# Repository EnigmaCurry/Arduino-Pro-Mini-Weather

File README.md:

Arduino Pro-Mini Enviromental Display Project
========================

This is an arduino project to build a miniature environment sensor
module to display temperature, barometric pressure, and humidity.

All files contained herein produced by
[R&TPreppers](https://www.youtube.com/channel/UCTNV_Oh5QAi1Is9r9Aw5bpw)
/ [njsharkracer](https://github.com/njsharkracer)

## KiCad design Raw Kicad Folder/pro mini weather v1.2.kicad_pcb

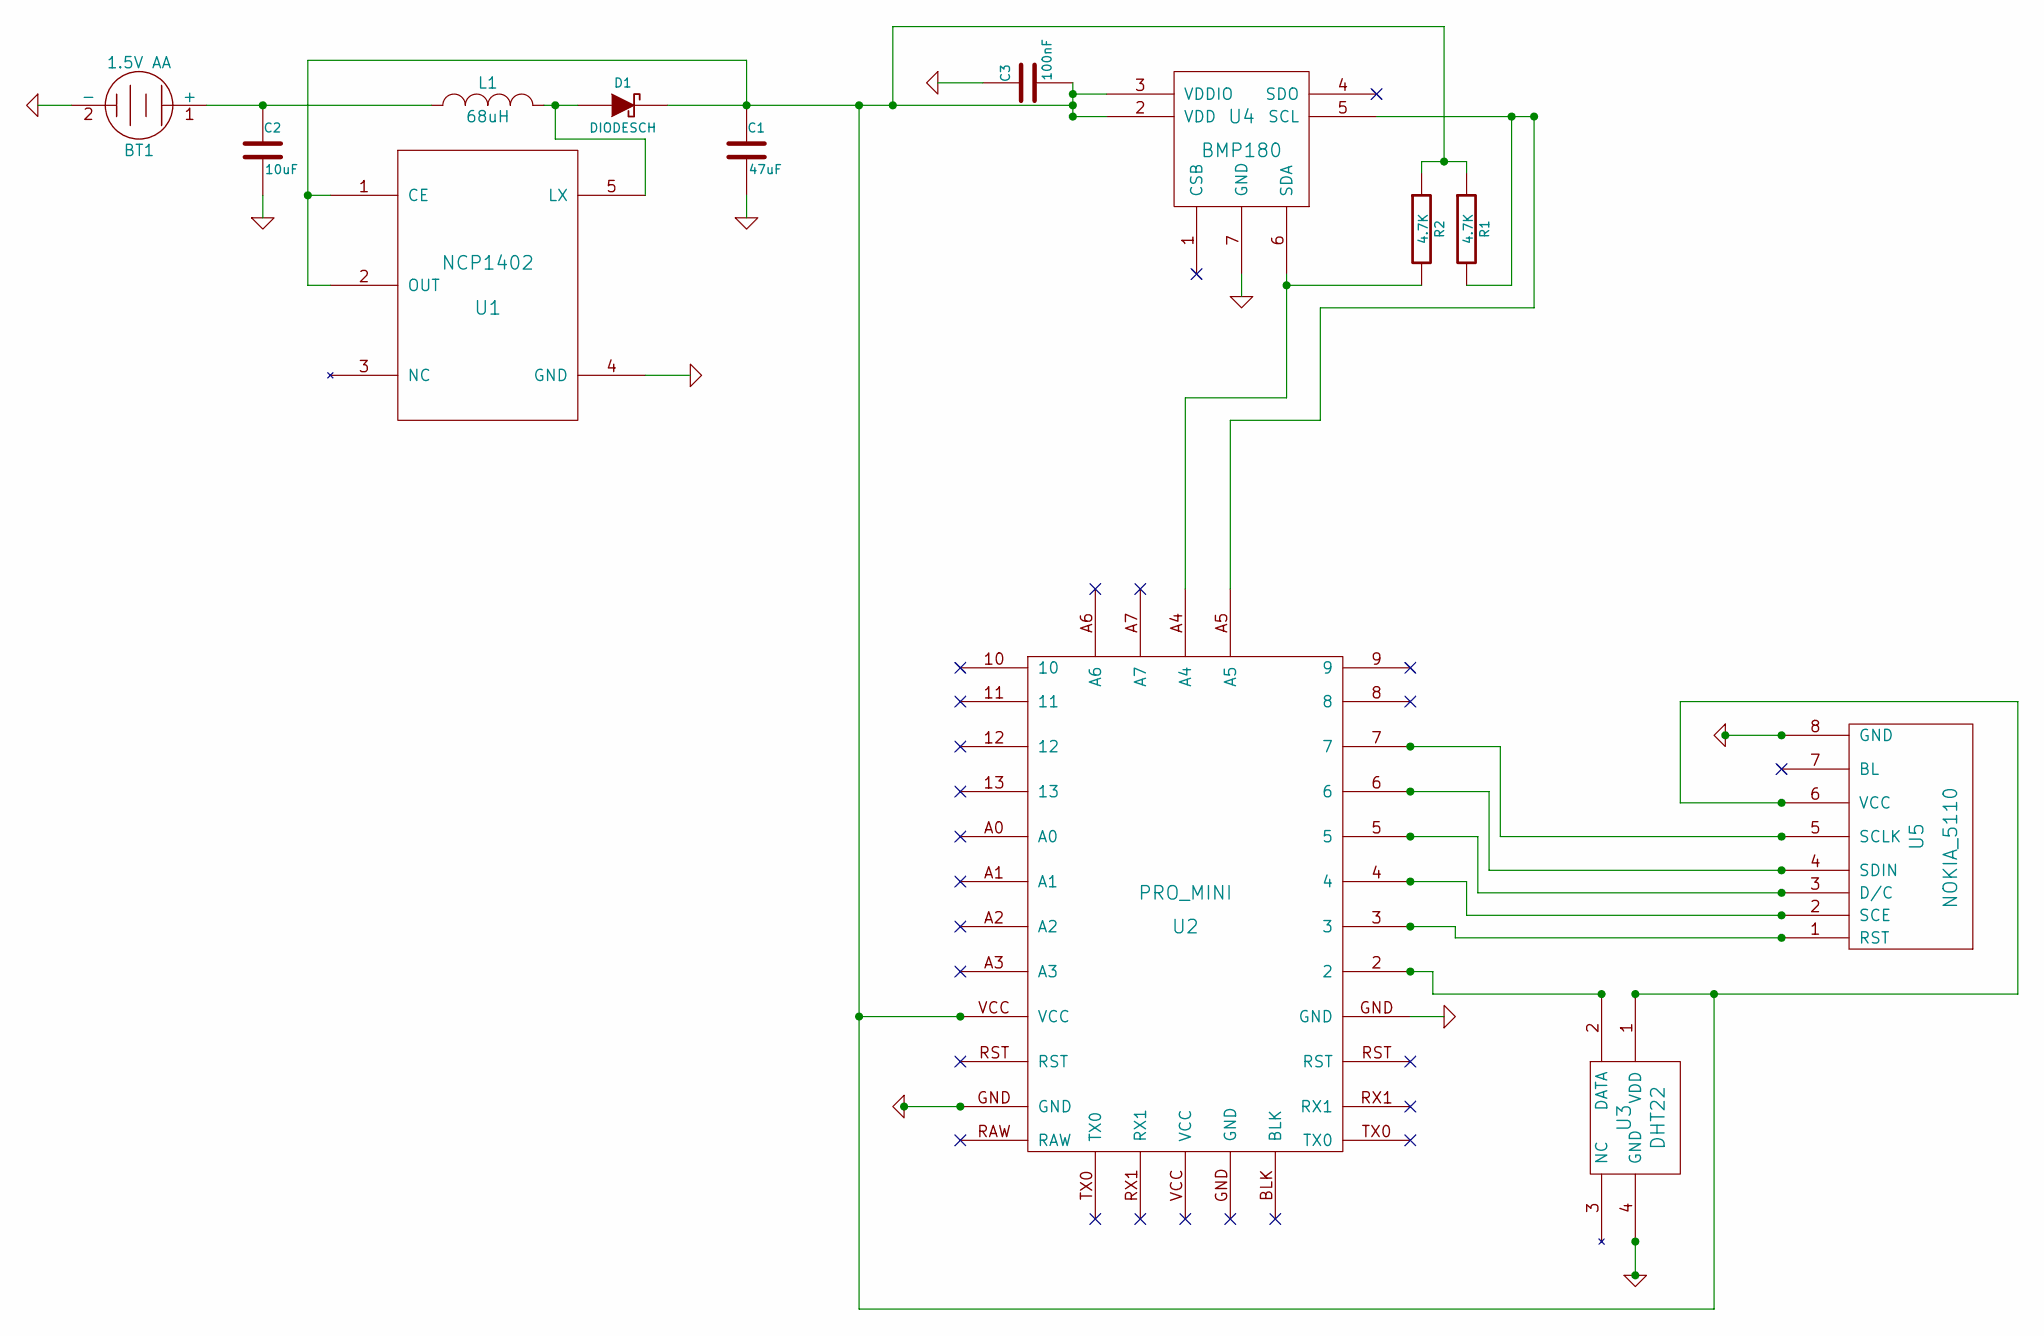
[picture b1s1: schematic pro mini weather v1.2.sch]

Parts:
BT1: 1.5V AA
C1: 47uF
C2: 10uF
C3: 100nF
D1: DIODESCH
L1: 68uH
R1, R2: 4.7K
U1: NCP1402
U2: PRO_MINI
U3: DHT22
U4: BMP180
U5: NOKIA_5110

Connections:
GND: BT1.2 (-), C1.2, C2.2, C3.1, U1.4 (GND), U2.GND, U3.4 (GND), U4.7 (GND), U5.8 (GND)
unnamed: D1.1 (A), L1.2, U1.5 (LX)
unnamed: R2.2, U2.A4, U4.6 (SDA)
unnamed: R1.2, U2.A5, U4.5 (SCL)
unnamed: C1.1, C3.2, D1.2 (K), R1.1, R2.1, U1.1 (CE), U1.2 (OUT), U2.VCC, U3.1 (VDD), U4.2 (VDD), U4.3 (VDDIO), U5.6 (VCC)
unnamed: U2.2, U3.2 (DATA)
unnamed: U2.3, U5.1 (RST)
unnamed: U2.5, U5.3 (D/C)
unnamed: U2.6, U5.4 (SDIN)
unnamed: U2.7, U5.5 (SCLK)
unnamed: U2.4, U5.2 (SCE)
unnamed: BT1.1 (+), C2.1, L1.1

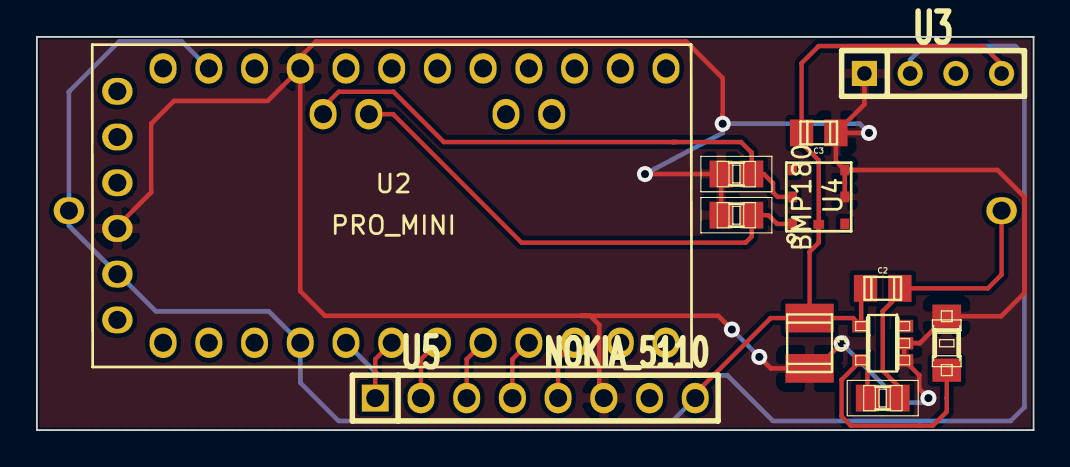
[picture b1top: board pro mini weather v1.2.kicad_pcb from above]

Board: 2 copper layers, 55.4 x 21.8 mm, 13 parts (1 on the bottom side), 12 nets.

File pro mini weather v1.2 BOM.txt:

| BT1        1.5V AA     AA Battery Holder
| C1         47uF        1210
| C2         10uF        0805
| C3         100nF       0805
| D1         DIODESCH    SOD-123
| L1         68uH        0805
| R1         4.7K        0805
| R2         4.7K        0805
| U1         NCP1402     SOT23-5
| U2         PRO_MINI    Sparkfun pro mini 5V 16Mhz
| U3         DHT22       Through Hole
| U4         BMP180      Custom Footprint
| U5         NOKIA_5110  Through Hole

If you want to order the boards directly through OSHPark:

https://oshpark.com/profiles/rtpreppers

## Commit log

2014-09-19 Initial project imported from dropbox - https://www.dropbox.com/sh/zk321hhf6tq8pfc/AADscaeXfx0vnkWLHbaOwZbTa?dl=0
